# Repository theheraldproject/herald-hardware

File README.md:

# Herald Hardware

Permissively licensed opensource hardware designs for Herald powered wearables and beacons. 
Supports digital contact tracing and other eHealth approaches.

## What is in this repository?

This repository aims to provide opensource hardware designs that can be used either
as-is or with modification by any Public Health Authority (PHA), NGO working on
disease outbreaks, or commercial company.

Several envisaged uses for these hardware designs are possible. 
The initial design targets include:-

- Digital Contact Tracing dedicated wearable
- Bluetooth venue beacon hardware as an alternative to manual check-in QR codes for bars, restaurants, etc.
- Digital Contact Tracing exposure tokens upload/download gateway links for remote communities
- Health monitoring wearable

We aim to provide a range of design files in this repository, including:-

- Hardware design overview descriptions
- Datasheets for designs
- Electronics schematics
- PCB layouts
- BOM files for designs

Our [Main website](https://vmware.github.io/herald/) will contain documentation
including quick start guides and application development guides.

Software and sample applications to run on this hardware can be found on
the main Herald Proximity project website.

## What hardware are your designs based on?

Our main hardware platform are Nordic Semiconductor's nRF52 and 53 series
SoCs. In particular the nRF52833 provides a good balance between
memory availability and processing power.

We also use Nordic Semiconductor's nRF Connect SDK (NCS), which is based
on the Zephyr RTOS, as our target Operating System.

Herald's C++ API and samples are first tested on nRF52832DK, nRF52833DK,
nRF52840DK and nRF5340DK, and then tested on the hardware designs in this
repository.

## Are any custom drivers needed?

We have created some custom Zephyr drivers based on our own sensor needs.
We will be contributing these to upstream Zephyr as PRs. This process may
take some time. If you cannot compile our demo apps for your device then
please visit the Zephyr Devices repository from The Herald Project at 
the below URL:

https://github.com/theheraldproject/zephyr-devices

## License and Copyright

This repository is licensed under CERN-OHL-P v2.

More information on this license can be found in LICENSE.txt or at 
https://ohwr.org/project/cernohl/wikis/Documents/CERN-OHL-version-2

All files in the external/ subdirectory are covered by distribution
terms of their respectable owners.

All works are copyright 2021 Herald Project Contributors. See the
NOTICE.txt file for details.

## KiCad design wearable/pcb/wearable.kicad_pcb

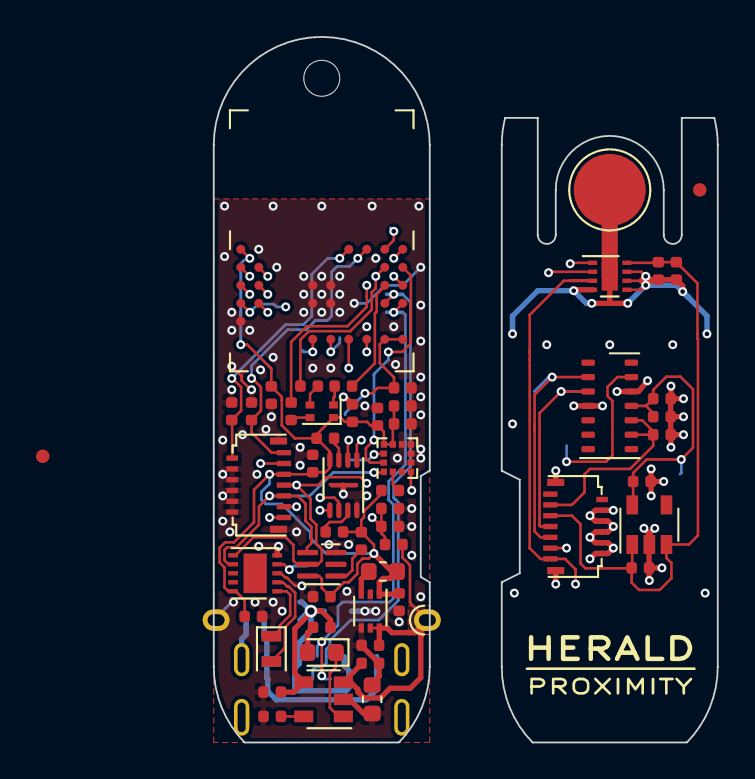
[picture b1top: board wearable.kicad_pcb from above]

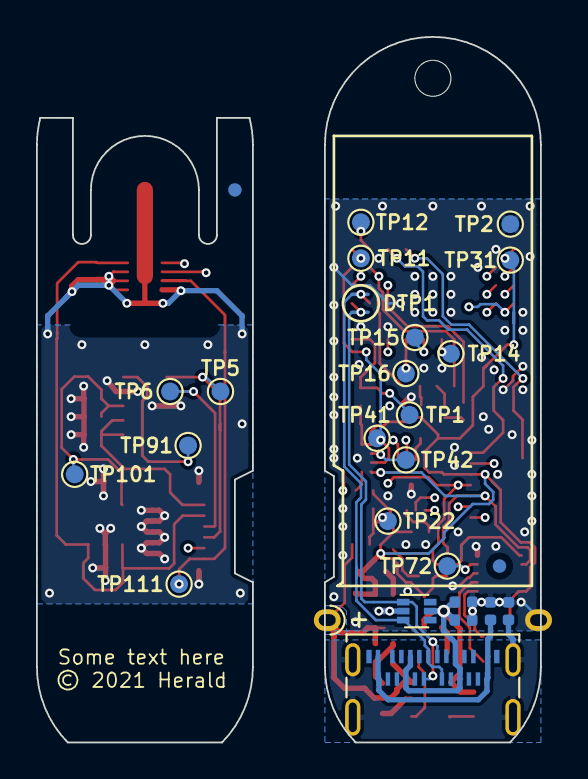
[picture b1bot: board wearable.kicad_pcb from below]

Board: 4 copper layers, 28.0 x 39.2 mm, 82 parts (26 on the bottom side), 47 nets.

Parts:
BT1: LiPo; Herald_Battery_Solder_Pads
C1, C11, C12, C21, C22, C112: 4.7uF; C_0402_1005Metric
C2: 100nF/100V; C_0402_1005Metric
C3, C31, C32, C41, C91, C93: 10uF; C_0402_1005Metric
C13, C14: 390pF; C_0402_1005Metric
C23: 10nF; C_0402_1005Metric
C42, C43, C61, C71, C92, C111: 100nF; C_0402_1005Metric
C51, C101, C102: 1uF; C_0402_1005Metric
D1: LED_ARBG; LED_Kingbright_APHF1608
D2: CHSTAT; LED_0603_1608Metric
FB1, FB2: 120R/0.6A; L_0402_1005Metric
FID1, FID2, FID3, FID4: Fiducial; Fiducial_0.75mm_Mask1.5mm
H1: MountingHole; MountingHole_2mm
H2: ThermalSlot; MillSlot_8.0x1.0mm
J1: USB_C_Receptacle_USB2.0; USB_C_Receptacle_IPxx
J2, J3: Extension; TE_1-2328724-3_2Rows_13Pins_P0.3mm_Horizontal
L31: 2.2uH; L_0603_1608Metric
R1: 0; R_0402_1005Metric
R2: 3.9k; R_0402_1005Metric
R3: 1k; R_0402_1005Metric
R4: 0; R_0603_1608Metric
R21, R41, R51, R61, R62: 10k; R_0402_1005Metric
R22: 5.6k; R_0402_1005Metric
R23: 6.8M; R_0402_1005Metric
R24: 10M; R_0402_1005Metric
TP1: VBUS; TestPoint_Pad_D1.0mm
TP2: GND; TestPoint_Pad_D1.0mm
TP5: SCL; TestPoint_Pad_D1.0mm
TP6: SDA; TestPoint_Pad_D1.0mm
TP11: SWDIO; TestPoint_Pad_D1.0mm
TP12: SWDCLK; TestPoint_Pad_D1.0mm
TP14: MISO; TestPoint_Pad_D1.0mm
TP15: MOSI; TestPoint_Pad_D1.0mm
TP16: SCLK; TestPoint_Pad_D1.0mm
TP22: BTSTAT; TestPoint_Pad_D1.0mm
TP31: VDD; TestPoint_Pad_D1.0mm
TP41: ACCINT1; TestPoint_Pad_D1.0mm
TP42: ACCINT2; TestPoint_Pad_D1.0mm
TP72: RTCINT; TestPoint_Pad_D1.0mm
TP91: BIOINT; TestPoint_Pad_D1.0mm
TP101: 1V8; TestPoint_Pad_D1.0mm
TP111: TMPINT; TestPoint_Pad_D1.0mm
TP112: ThPad; TestPoint_Pad_D4.0mm
U1: BC833; Fanstel_BC833x
U2: MCP73832-2-OT; SOT-23-5
U3: S-85S1A; SNT-6A
U4: LIS2DE12; LGA-12_2x2mm_P0.5mm
U5: APDS-9250; Broadcom_DFN-6_2x2mm_P0.65mm
U6: MX25R8035FZxxx0; USON-8-1EP_2x3mm_P0.5mm_EP0.25x1.65mm
U7: PCF85063ATL; DFN-10-1EP_2.6x2.6mm_P0.5mm_EP1.25x2.15mm
U8: DT1446-04V; SOT-563
U9: MAX30102; Maxim_OLGA-14_3.3x5.6mm_P0.8mm
U10: TCR3UFxxA; SOT-23-5
U11: TMP1075; WSON-8-1EP_2x2mm_P0.5mm_EP0.9x1.6mm
Y71: 32.768kHz; Crystal_SMD_2012-2Pin_2.0x1.2mm

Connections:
+1V8: C91.1, C92.1, C102.1, TP101.1, U9.11, U10.5
+BATT: BT1.1, C22.2, C31.1, J2.11, R23.1, U2.3, U3.5, U3.6
/Core Board/ACC_INT1: TP41.1, U1.17, U4.12
/Core Board/ACC_INT2: TP42.1, U1.4, U4.11
/Core Board/BIO_INT: J2.3, U1.2
/Core Board/BT_STAT: C23.1, R23.2, R24.1, TP22.1, U1.6
/Core Board/CH_STAT: D2.1, U2.1
/Core Board/FLASH_CS: U1.7, U6.1
/Core Board/FLASH_RST: R61.2, U6.7
/Core Board/FLASH_WP: R62.2, U6.3
/Core Board/LED_B: R1.1, U1.21
/Core Board/LED_G: R2.1, U1.16
/Core Board/LED_R: R3.1, U1.20
/Core Board/LS_INT: R51.2, U5.4
/Core Board/MISO: TP14.1, U1.9, U6.2
/Core Board/MOSI: TP15.1, U1.10, U6.5
/Core Board/NFC1: C13.1, J2.13, U1.23
/Core Board/NFC2: C14.1, J2.12, U1.24
/Core Board/RTC_INT: TP72.1, U1.3, U7.4
/Core Board/SCL: J2.5, U1.12, U4.1, U5.1, U7.7
/Core Board/SCLK: TP16.1, U1.11, U6.6
/Core Board/SDA: J2.7, U1.8, U4.4, U5.2, U7.6
/Core Board/SWDCLK: TP12.1, U1.22
/Core Board/SWDIO: TP11.1, U1.18
/Core Board/USB_D+: J1.A6, J1.B6, U1.19, U8.3
/Core Board/USB_D-: J1.A7, J1.B7, U1.15, U8.1
/Extension Board/BIO_INT: J3.11, TP91.1, U9.13
/Extension Board/SCL: J3.9, TP5.1, U9.2, U11.2
/Extension Board/SDA: J3.7, TP6.1, U9.3, U11.1
/Extension Board/TMP_INT: J3.13, TP111.1, U11.3
Earth: FB1.1, J1.S1
GND: BT1.2, C1.1, C2.1, C3.2, C11.2, C12.2, C13.2, C14.2, C21.1, C22.1, C23.2, C31.2, C32.2, C41.2, C42.2, C43.2, C51.2, C61.1, C71.2, FB1.2, FB2.2, J2.2, J2.4, J2.6, J2.8, J2.10, J2.MP, R4.1, R4.2, R21.2, R24.2, TP2.1, U1.5, U1.25, U1.26, U1.27, U1.28, U2.2, U3.2, U3.4, U4.5, U4.6, U4.7, U4.8, U5.6, U6.4, U6.EP, U7.3, U7.5, U8.2
GND1: C91.2, C92.2, C93.2, C101.2, C102.2, C111.1, C112.1, J3.4, J3.6, J3.8, J3.10, J3.12, J3.MP, TP112.1, U9.4, U9.12, U10.2, U11.4, U11.5, U11.6, U11.7, U11.9
GNDPWR: FB2.1, J1.A1, J1.A12, J1.B1, J1.B12
unnamed: D1.2, R3.2
unnamed: D1.3, R1.2
unnamed: D1.4, R2.2
unnamed: D2.2, R22.1
unnamed: L31.2, U3.3
unnamed: R21.1, U2.5
unnamed: R41.2, U4.2
unnamed: U7.1, Y71.1
unnamed: U7.2, Y71.2
VBUS: C1.2, C2.2, C11.1, C21.2, J1.A4, J1.A9, J1.B4, J1.B9, R22.2, TP1.1, U1.13, U1.14, U2.4, U8.5
VDD: C3.1, C12.1, C32.1, C41.1, C42.1, C43.1, C51.1, C61.2, C71.1, D1.1, J2.9, L31.1, R41.1, R51.1, R61.1, R62.1, TP31.1, U1.1, U3.1, U4.9, U4.10, U5.3, U6.8, U7.10
VDD1: C101.1, C111.2, C112.2, J3.5, U10.1, U10.3, U11.8
Vdrive: C93.1, J3.3, U9.9, U9.10

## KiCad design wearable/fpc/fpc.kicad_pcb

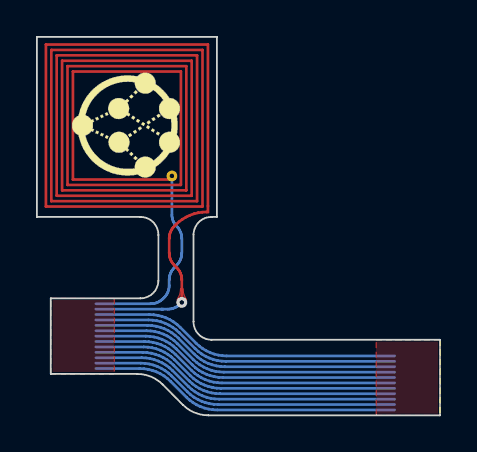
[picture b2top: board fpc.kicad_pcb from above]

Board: 2 copper layers, 22.4 x 21.0 mm, 3 parts (0 on the bottom side), 9 nets.

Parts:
AE1: NFC; NFC_9x9mm_T6_W0.15mm_P0.3mm
J1, J2: FPC; TE_1-2328724-3_2Rows_13Pins_P0.3mm_FPC

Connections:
/BATT: J1.11, J2.3
/BIO_INT: J1.3, J2.11
/NFC1: AE1.2, J1.12
/NFC2: AE1.1, J1.13
/SCL: J1.5, J2.9
/SDA: J1.7, J2.7
/TMP_INT: J1.1, J2.13
/VDD: J1.9, J2.5
GND: J1.2, J1.4, J1.6, J1.8, J1.10, J2.4, J2.6, J2.8, J2.10, J2.12

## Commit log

2021-03-24 README and LICENSE added
2021-03-31 Create DCO-trigger
2021-04-08 Fixes #3. Added LFPH required project files.
2021-04-12 Initial import of the Herald Wearable Beacon hardware files.
    The device can be used as both a weareable or a beacon. It features
    nRF52833 SoC packaged in BC833M module, flash memory, and number
    of sensors, including:
    - accelerometer for device control
    - four-channel light sensor for environment sensing
    - pulse oximeter and temperature sensors for health monitoring
2021-04-12 Add 3D models of the USB-C and FPC connectors.
    The models are derived from the STEP files provided by the Amphenol/ICC
    and the TE Connectivity. Please see external/README for details.
2021-04-12 Provide 3D model for housing for the Wearable/Beacon.
2021-04-12 Work out the fabrication layers.
2021-04-13 Fixes #6. Added PCB boards image
    Fixes #6.
2021-04-14 Import the FPC+NFC ribbon cable.
    The cable connects top and bottom boards, and offers an NFC antenna.
2021-04-15 The bill of materials has been completed.
    While working on the BoM, fix error in the battery sensing circuit.
    The R23 must be 6.8M or bigger (previously was 4M). This is required
    to keep the ADC voltage below VDD=2.5V value.
2021-04-15 Some BoM fixes popped up after uploading it to the Octopart.
2021-05-05 Wearable renders: fix the USB charging LED.
2021-05-05 Review the wearable ribbon cable for manufacturing.
    - Do teardrops at vias.
    - Make it up with logo & copyright text.
2021-05-15 Nordic Review: make ground area on the top layer solid.
    To acheive this, route NFC traces on the bottom size, make the
    BC833M pad connection to zones solid, and move some test points
    across the board.
    Also, temporarily remove the front fiducial from the core board.
    It will be placed later when the boards will get panelized.
2021-05-24 Adjust the BoM to include only the stocked components.
2021-05-27 Completely rework the temperature sensor layout.
    Now, use a dedicated thermal guide to the IC exposed pad, and
    decouple the sensor from the rest of the board.
2021-05-28 Make pcbnew DRC happy.
    This improves pad-to-pad clearance for the SOT-563 packages,
    and allows overlapping footprints (yep, real estate is expenisve).
2021-05-28 Create in-housing thermal guide to the TMP1075 sensor.
2021-07-19 Nordic review: drop current limiting resitors from the USB.
    Per @msromero: For D+ and D- lines it's recommend to get rid of the
    22R resistors in parallel of the TVS diodes, since you can risk
    failing USB testing.
    Thanks!
2021-07-19 Mark thermal slots/pads in the BoM accordingly.
2021-07-19 Tune the LED resistors.
    The RGB LED resistors were tuned on a real board with 2.5V driver
    voltage. It happens the blue LED should be zero Ohm limited, and
    then red and green LEDs adjusted to the neutral white.
    The charge LED looks good with 5.1k, but more standard 5.6k should
    also work just fine.
2021-07-21 Tune the NFC antenna.
    The antenna design is in the wearable/fpc directory.
    S11: https://twitter.com/mishkathebear/status/1417551022650691590/photo/1
2021-07-23 Describe electrical configuration of the interrupt lines.
2021-09-29 Improve the USB receptacle fitting inside the housing.

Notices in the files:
wearable/fpc/fpc.kicad_pcb:
© 2021 Herald Project Contributors
Licensed under CERN-OHL-P version 2
© 2021 Herald
